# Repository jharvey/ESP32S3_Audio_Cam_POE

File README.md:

# ESP32S3_Audio_Cam_POE

This is a PCB layout for ESP32S3 with OV2640 / OV5640 camera. It was designed in KiCad 9 and converted to KiCad 10 (10.0.8); the files no longer open in KiCad 9.
The board's major features include:
* Camera.
* 2 way audio.
* Hardwired Ethernet including POE.
* Camera pan / tilt servos and lamp control.
* record to SD card.
* misc outputs to drive misc motors or similar outputs. 
* Battery powered option with Li-ion type of battery. 
* Stream video to NVR recording station. 

## Firmware
Firmware found here https://github.com/jharvey/ESP32-CAM_MJPEG2SD

Changes up to version 0.1:
* Initial layout
* Converted to KiCad 10.
* Removed the Medium and Smaller cost-reduction variants.

## Purpose

The layout design intent is to make a hardwired intercom system which includes options for camera, making a near equivalent of a doorbell camera. Hardwired means it's not susceptible to RF jamming, or similar attacks. It can be battery powered at the ethernet switch source so it can handle power outages. Lighting controls allow night time spot light, and day time spot light controls. Pan, Tilt, Rotate could potentially allow a laser pointer to distract bad players if things go bump in the night. 

## Installation
Clone with the JLCPCB library submodule, which the symbol and footprint tables point to:

```
git clone --recurse-submodules https://github.com/jharvey/ESP32S3_Audio_Cam_POE.git
```

All JLCPCB symbols, footprints and 3D models resolve from this submodule, so you do not need the JLCPCB library installed through the KiCad Plugin and Content Manager. Other 3D models use KiCad's standard `${KICAD10_3DMODEL_DIR}` library.

On Windows, if the submodule fails with "Filename too long" or "'$GIT_DIR' too big", enable long paths first (`git config --global core.longpaths true`) or clone to a shorter folder.

TBD currently has not had its first spin. TBD

## 3D case
See 3D case found here
TBD create file in OnShape and post link here. TBD

## 3D pictures from KICAD
<div align="center">

</div>

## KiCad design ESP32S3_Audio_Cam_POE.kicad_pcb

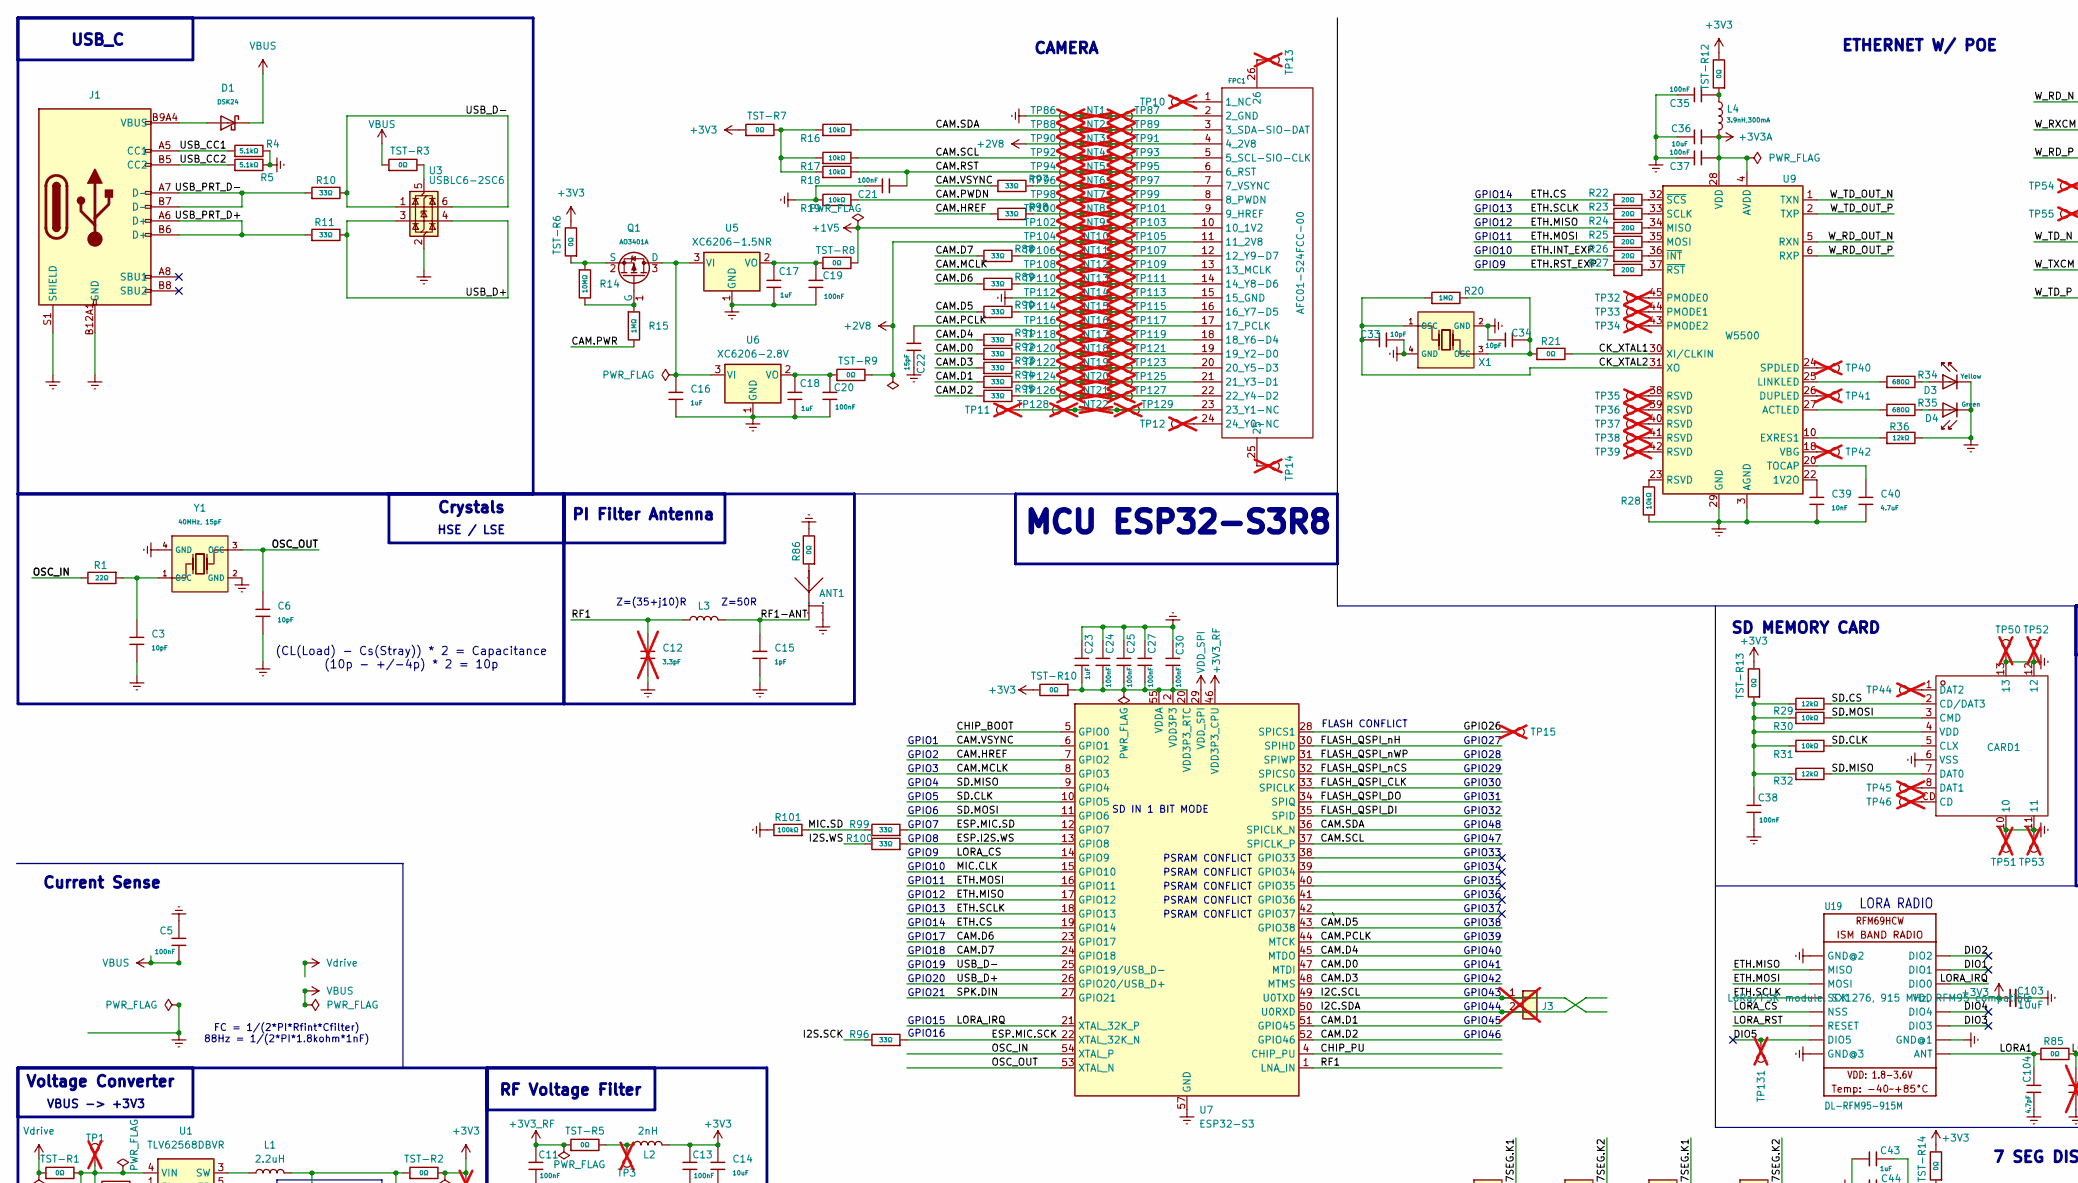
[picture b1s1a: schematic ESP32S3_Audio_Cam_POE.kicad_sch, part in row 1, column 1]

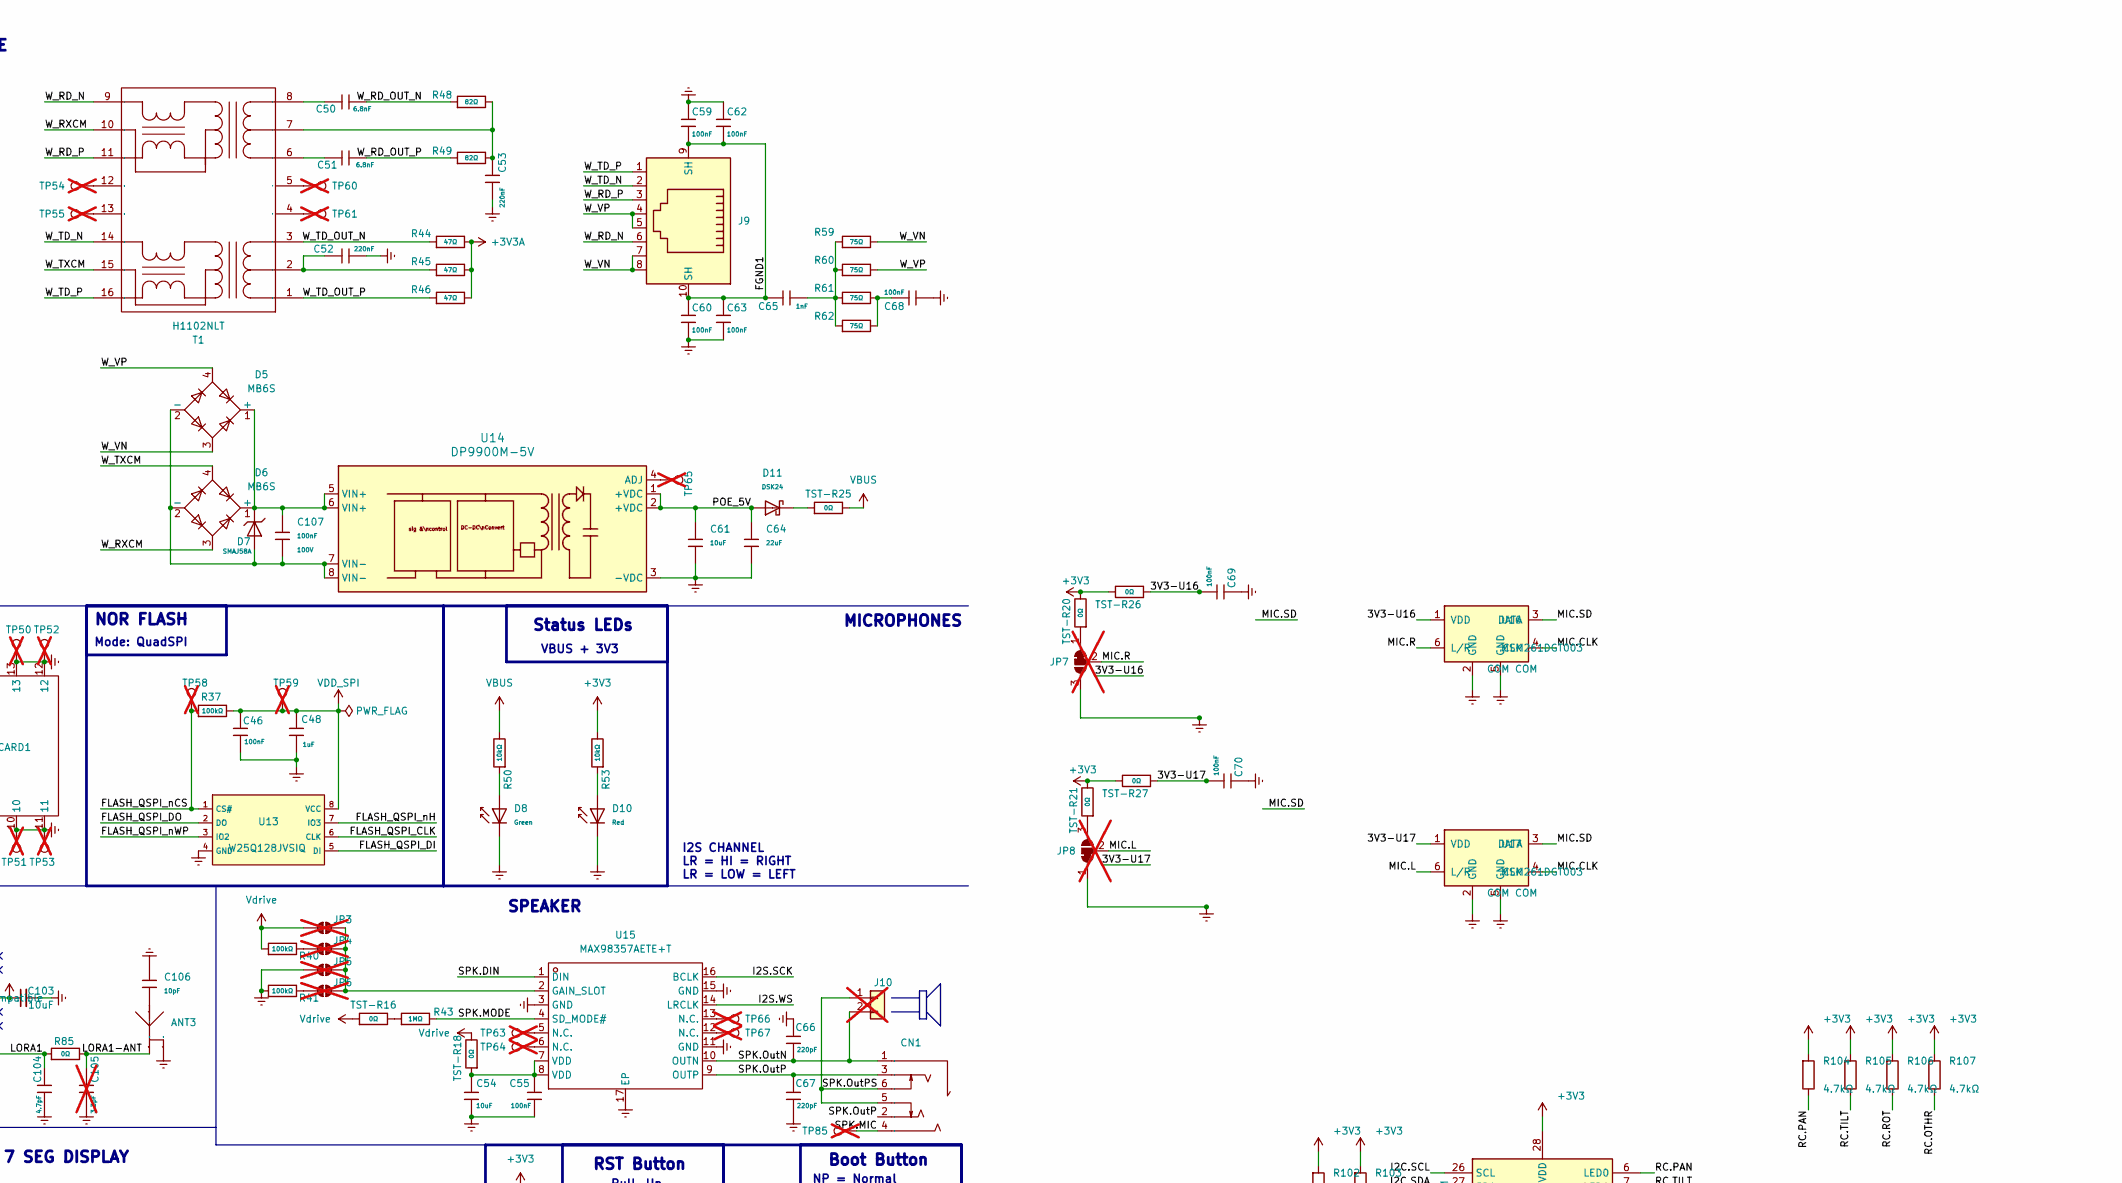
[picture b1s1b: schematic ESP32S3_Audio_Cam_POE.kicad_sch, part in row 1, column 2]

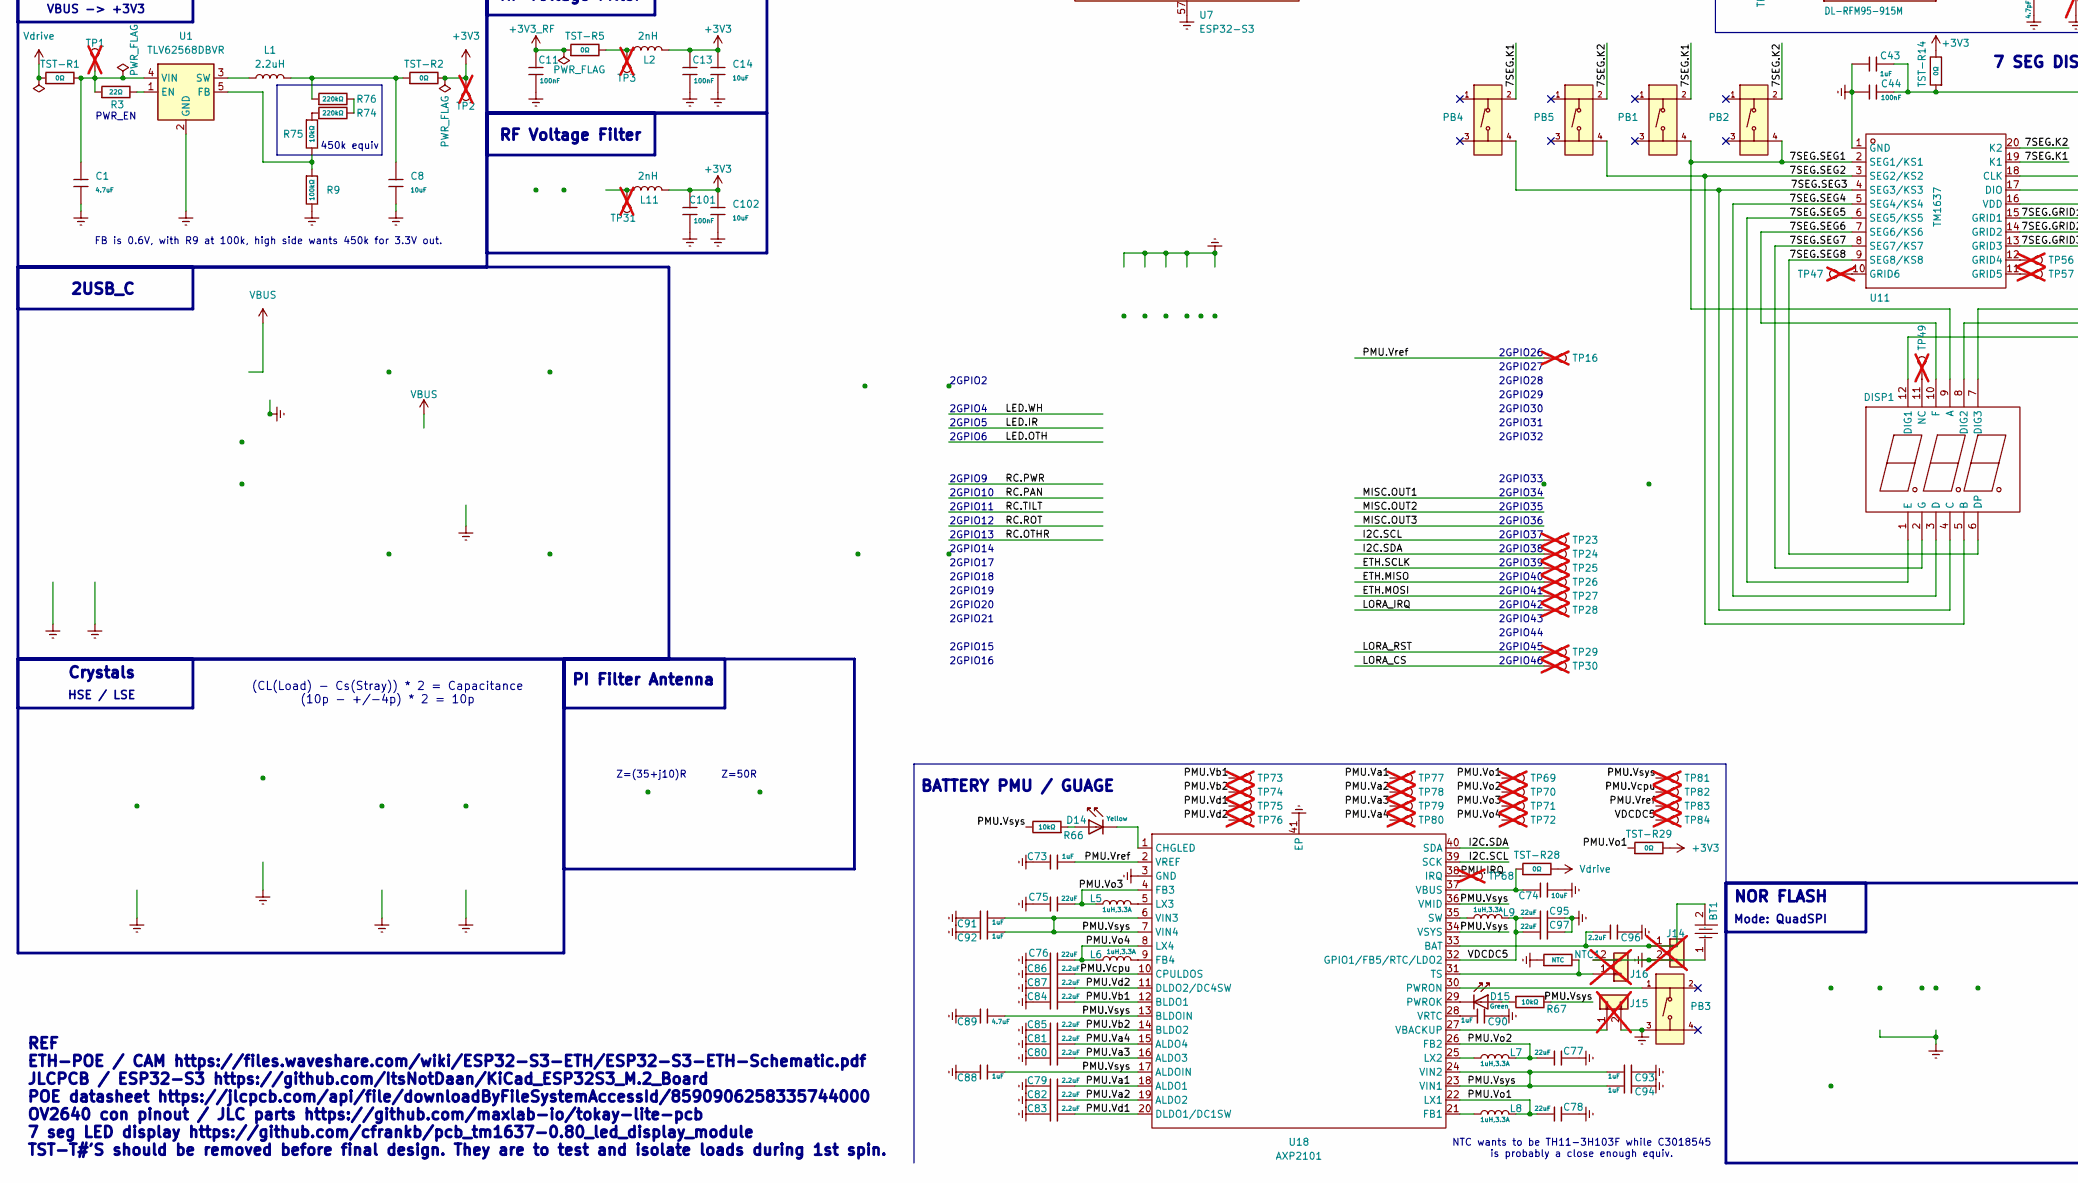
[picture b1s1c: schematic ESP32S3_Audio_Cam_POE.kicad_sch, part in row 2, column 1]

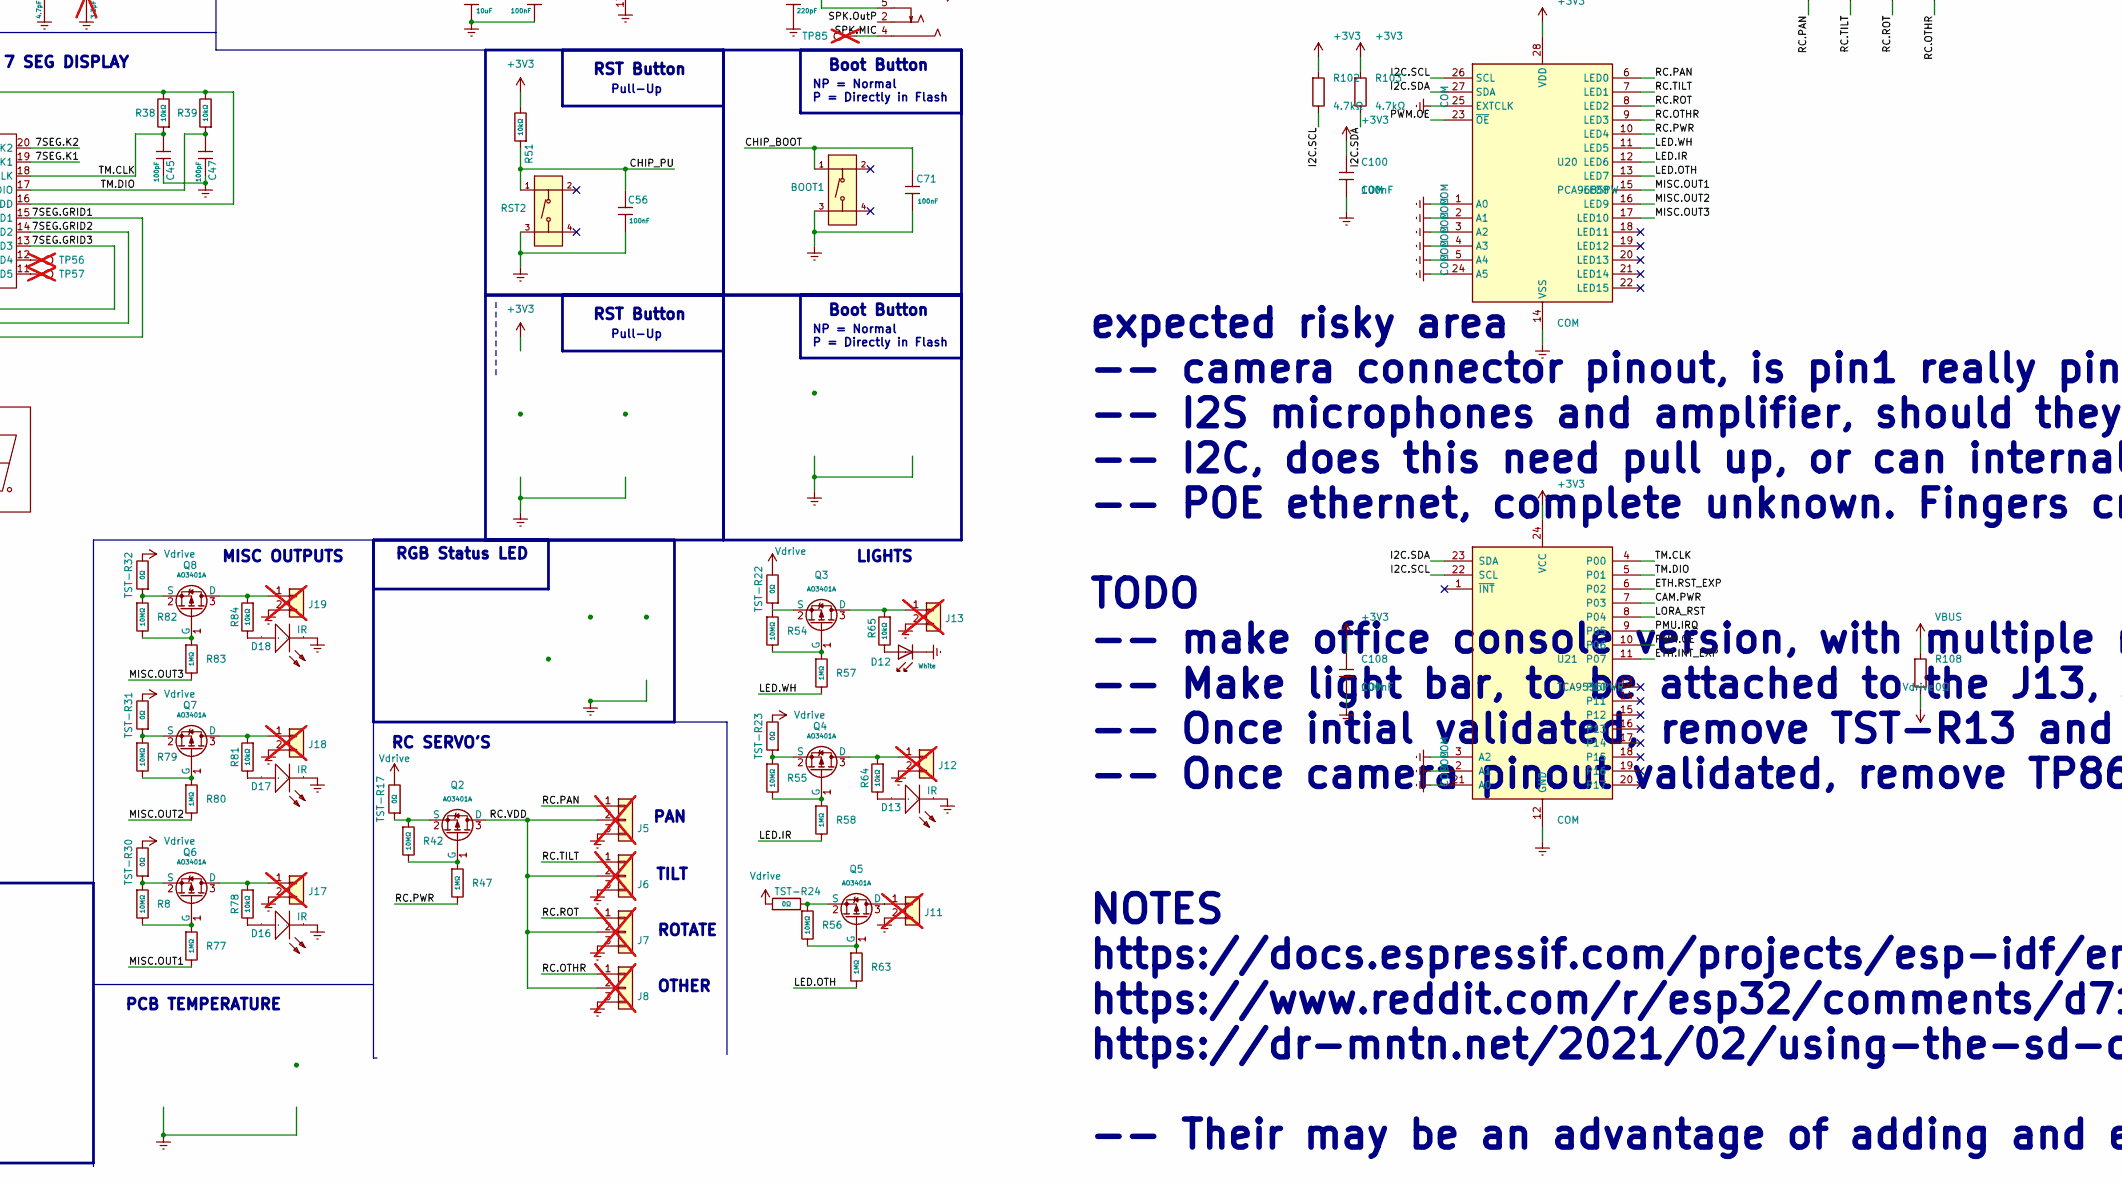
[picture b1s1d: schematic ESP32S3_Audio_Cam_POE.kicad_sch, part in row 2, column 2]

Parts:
ANT1: KH-3216-H0209; ANT-SMD_L3.2-W1.6-KH-3216F245C04; LCSC C2925417
ANT3: H2U646MHLQ0200; ANT-SMD_H2U646MHLQ0200; LCSC C5370061
BOOT1: Tactile Button, 160gf; SW-SMD_4P-L5.1-W5.1-P3.70-LS6.5-TL-2; LCSC C318884
BT1: BH-18650-B1BA002; BATTERY-SMD_18650-1S-L77.1-W20.7-1; LCSC C2988620
C1: 4.7uF; C_0805; LCSC C1779
C3, C6, C33, C34, C106: 10pF; C_0402; LCSC C32949
C5, C11, C13, C19, C20, C21, C24, C25, C27, C30, C35, C37, C38, C44, C46, C55, C56, C68, C69, C70, C71, C101: 100nF; C_0603; LCSC C14663
C8, C14, C74, C102: 10uF; C_0402; LCSC C15525
C12, C105: 3.3pF; C_0402; LCSC C1565; not fitted
C15: 1pF; C_0402; LCSC C1550
C16, C17, C18, C23, C43, C48: 1uF; C_0603; LCSC C15849
C22: 15pF; C_0402; LCSC C1548
C36, C54, C61, C103: 10uF; C_0805; LCSC C440198
C39: 10nF; C_0402; LCSC C15195
C40: 4.7uF; C_0603; LCSC C19666
C45, C47: 100pF; C_0402; LCSC C1546
C50, C51: 6.8nF; C_0603; LCSC C1631
C52, C53: 220nF; C_0603; LCSC C21120
C59, C60, C62, C63: 100nF; C_0805; LCSC C28233
C64: 22uF; C_0805; LCSC C45783
C65: 1nF; C_1206; LCSC C9196
C66, C67: 220pF; C_0402; LCSC C1530
C73, C88, C90, C91, C92, C93, C94: 1uF; C_0402; LCSC C52923
C75, C76, C77, C78, C95, C97: 22uF; C_0603; LCSC C59461
C79, C80, C81, C82, C83, C84, C85, C86, C87, C96: 2.2uF; C_0402; LCSC C12530
C89: 4.7uF; C_0402; LCSC C23733
C100, C108: 100nF; C_0603
C104: 4.7pF; C_0402; LCSC C1569
C107: 100nF; C_0805; Voltage Rated 100V; Tolerance ±10%; Part CL21B104KCFNNNE; LCSC C28233
CARD1: TF PUSH; TF-PUSH-SD-CARD_C393941; LCSC C393941
CN1: PJ-316C-6A; SMD_3.5mm_Audio_Connectors_(Headphones)_C707223; LCSC C707223
D1, D11: DSK24; D_SOD-123FL; LCSC C22466352
D3, D14: Yellow; D_0805; LCSC C2296
D4, D8, D15: Green; D_0805; LCSC C2297
D5, D6: MB6S; MB6S-C82584; LCSC C82584
D7: SMAJ58A; D_SMA; LCSC C19077554
D10: Red; D_0603; LCSC C2286
D12: White; D_0603; LCSC C2290
D13, D16, D17, D18: IR; IR-LED_C131280; LCSC C131280
DISP1: SLS0563DBA1GD; 3x7-seg_LED-RED_C2913084; LCSC C2913085
FPC1: AFC01-S24FCC-00; OV2640_connector_AFC01-S24FCC-00; LCSC C262276
J1: Connector, USB-TYPE-C-16P; TYPE-C-SMD_HX-TYPE-C-16PIN; LCSC C2927039
J3, J10, J11, J12, J13, J14, J15, J16, J17, J18, J19: Conn_01x02; PinHeader_1x02_P1.00mm_Vertical; not fitted
J5, J6, J7, J8: Conn_01x03; PinHeader_1x03_P2.54mm_Vertical; not fitted
J9: HC-RJ45-055-4_8P8C_Shielded; HC-RJ45-055-4_C3000211; LCSC C3000211
JP3, JP4, JP5, JP6: SolderJumper_2_Open; SolderJumper-2_P1.3mm_Open_TrianglePad1.0x1.5mm; not fitted
JP7, JP8: SolderJumper_3_Bridged12; SolderJumper-3_P1.3mm_Bridged12_Pad1.0x1.5mm; not fitted
L1: 2.2uH; L_Wurth_WE-LQSH-4020; LCSC C135262
L2, L11: 2nH; L_0603_1608Metric_Pad1.05x0.95mm_HandSolder; LCSC C29682
L3, L4: 3.9nH,300mA; L_0402; LCSC C14033
L5, L6, L7, L8, L9: 1uH,3.3A; L_1008_2520Metric; LCSC C435392
NT1, NT2, NT3, NT4, NT5, NT6, NT7, NT8, NT9, NT10, NT11, NT12, NT13, NT14, NT15, NT16, NT17, NT18, NT19, NT20, NT21, NT22: NetTie_2; NetTie-2_SMD_Pad0.5mm; not fitted
NTC1: NTC; R_0402; LCSC C3018545
PB1, PB2, PB3, PB4, PB5: Tactile Button, 160gf; SW-SMD_4P-L5.1-W5.1-P3.70-LS6.5-TL-2; LCSC C318884
Q1, Q2, Q3, Q4, Q5, Q6, Q7, Q8: AO3401A; Q_SOT-23; LCSC C15127
R1, R3: 22Ω; R_0402; LCSC C25092
R4, R5: 5.1kΩ; R_0402; LCSC C25905
R8, R14, R42, R54, R55, R56, R79, R82: 10MΩ; R_0402; LCSC C26082
R9, R37: 100kΩ; R_0402; LCSC C25741
R10, R11: 33Ω; R_0402; LCSC C25105
R15, R20, R43, R47, R57, R58, R63, R77, R80, R83: 1MΩ; R_0402; LCSC C26083
R16, R17, R18, R19, R28, R30, R31, R38, R39, R50, R51, R53, R64, R65, R66, R67, R75, R78, R81, R84: 10kΩ; R_0402; LCSC C25744
R21, R85, R86: 0Ω; R_0402; LCSC C17168
R22, R23, R24, R25, R26, R27: 20Ω; R_0603; LCSC C22950
R29, R32, R36: 12kΩ; R_0603; LCSC C22790
R34, R35: 680Ω; R_0402; LCSC C25130
R40, R41: 100kΩ; R_0805; LCSC C149504
R44, R45, R46: 47Ω; R_0603; LCSC C23182
R48, R49: 82Ω; R_0603; LCSC C23255
R59, R60, R61, R62: 75Ω; R_0603; LCSC C4275
R74, R76: 220kΩ; R_0402; LCSC C25767
R88, R89, R90, R91, R92, R93, R94, R95, R96, R97, R98, R99, R100: 33Ω; R_0402; Overload Voltage (Max) 50V; Tolerance ±1%; Part 0402WGF330JTCE; LCSC C25105
R101: 100kΩ; R_0402; Overload Voltage (Max) 50V; Tolerance ±1%; Part 0402WGF1003TCE; LCSC C25741
R102, R103, R104, R105, R106, R107: 4.7kΩ; R_0402; LCSC C25900
R108: 0Ω; R_1206; LCSC C17888
RST2: Tactile Button, 160gf; SW-SMD_4P-L5.1-W5.1-P3.70-LS6.5-TL-2; LCSC C318884
T1: H1102NLT; H1102NLT_C18584; LCSC C18584
TP1, TP2, TP3, TP10, TP11, TP12, TP15, TP16, TP23, TP24, TP25, TP26, TP27, TP28, TP29, TP30, TP31, TP32, TP33, TP34, TP35, TP36, TP37, TP38, TP39, TP40, TP41, TP42, TP44, TP45, TP46, TP47, TP49, TP54, TP55, TP56, TP57, TP58, TP59, TP60, TP61, TP63, TP64, TP65, TP66, TP67, TP68, TP85, TP131: TestPoint; TestPoint_Pad_D1.0mm; not fitted
TP13, TP14, TP50, TP51, TP52, TP53: TestPoint; TestPoint_Plated_Hole_D2.0mm; not fitted
TP69, TP70, TP71, TP72, TP73, TP74, TP75, TP76, TP77, TP78, TP79, TP80, TP81, TP82, TP83, TP84, TP86, TP87, TP88, TP89, TP90, TP91, TP92, TP93, TP94, TP95, TP96, TP97, TP98, TP99, TP100, TP101, TP102, TP103, TP104, TP105, TP106, TP107, TP108, TP109, TP110, TP111, TP112, TP113, TP114, TP115, TP116, TP117, TP118, TP119, TP120, TP121, TP122, TP123, TP124, TP125, TP126, TP127, TP128, TP129: TestPoint; PinHeader_1x01_P1.00mm_Vertical; not fitted
TST-R1, TST-R2, TST-R3, TST-R5, TST-R6, TST-R7, TST-R8, TST-R9, TST-R10, TST-R12, TST-R13, TST-R14, TST-R16, TST-R17, TST-R18, TST-R20, TST-R21, TST-R22, TST-R23, TST-R24, TST-R25, TST-R26, TST-R27, TST-R28, TST-R29, TST-R30, TST-R31, TST-R32: 0Ω; R_0603; LCSC C21189
U1: TLV62568DBVR; SOT-23-5; LCSC C163219
U3: USBLC6-2SC6; SOT-23-6; LCSC C2827654
U5: XC6206-1.5NR; SOT-23-3; LCSC C2984869
U6: XC6206-2.8V; SOT-23-3; LCSC C41424780
U7: ESP32-S3; QFN-56-1EP_7x7mm_P0.4mm_EP4x4mm_ThermalVias; LCSC C2913194
U9: W5500; LQFP-48_7x7mm_P0.5mm; LCSC C32843
U11: TM1637; digital tube drivers_c2962580; LCSC C5337160
U13: W25Q128JVSIQ; SOIC-8_L5.3-W5.3-P1.27-LS8.0-BL; LCSC C97521
U14: DP9900M-5V; DP9900M_C5380106; LCSC C5380106
U15: MAX98357AETE+T; MAX98357AETE+T_C910544; LCSC C910544
U16, U17: MSM261DGT003; LGA-6_2.0x4.0mm_MSM261DGT003; LCSC C48227730
U18: AXP2101; QFN-40-1EP_5x5mm_P0.4mm_EP3.6x3.6mm_ThermalVias; LCSC C3036461
U19: DL-RFM95-915M; RFM69HCW; LCSC C2844473
U20: PCA9685PW; TSSOP-28_4.4x9.7mm_P0.65mm; LCSC C2678753
U21: TCA9555PWR; TSSOP-24_4.4x7.8mm_P0.65mm; LCSC C465732
X1: X322525MOB4SI; OSC-SMD_4P-L3.2-W2.5-BL; LCSC C9006
Y1: 40MHz, 15pF; OSC-SMD_4P-L3.2-W2.5-BL_SIT8008BI; LCSC C9010

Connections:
+1V5: NT9.1, TP102.1, TST-R8.2
+2V8: NT3.1, NT10.1, TP90.1, TP104.1, TST-R9.2
+3V3: C13.2, C14.1, C100.1, C101.2, C102.1, C103.1, C108.1, L2.2, L11.2, R51.2, R53.2, R102.1, R103.1, R104.1, R105.1, R106.1, R107.1, TP2.1, TST-R2.2, TST-R6.2, TST-R7.1, TST-R10.2, TST-R12.2, TST-R13.2, TST-R14.2, TST-R20.2, TST-R21.2, TST-R26.2, TST-R27.2, TST-R29.2, U19.5 (VDD), U20.28 (VDD), U21.24 (VCC)
+3V3A: C36.2, C37.2, L4.1, R44.2, R45.2, R46.2, U9.4 (AVDD), U9.8 (AVDD), U9.11 (AVDD), U9.15 (AVDD), U9.17 (AVDD), U9.21 (AVDD), U9.28 (VDD)
+3V3_RF: C11.2, TST-R5.1, U7.46 (VDD3P3_CPU)
/3V3-U16: C69.1, TST-R26.1, U16.1 (VDD)
/3V3-U17: C70.1, TST-R27.1, U17.1 (VDD)
/7SEG.GRID1: DISP1.12 (DIG1), U11.15 (GRID1)
/7SEG.GRID2: DISP1.8 (DIG2), U11.14 (GRID2)
/7SEG.GRID3: DISP1.7 (DIG3), U11.13 (GRID3)
/7SEG.K1: PB1.2 (B), PB4.2 (B), U11.19 (K1)
/7SEG.K2: PB2.2 (B), PB5.2 (B), U11.20 (K2)
/7SEG.SEG1: DISP1.9 (A), PB1.4 (D), PB2.4 (D), U11.2 (SEG1/KS1)
/7SEG.SEG2: DISP1.5 (B), PB5.4 (D), U11.3 (SEG2/KS2)
/7SEG.SEG3: DISP1.4 (C), PB4.4 (D), U11.4 (SEG3/KS3)
/7SEG.SEG4: DISP1.3 (D), U11.5 (SEG4/KS4)
/7SEG.SEG5: DISP1.1 (E), U11.6 (SEG5/KS5)
/7SEG.SEG6: DISP1.10 (F), U11.7 (SEG6/KS6)
/7SEG.SEG7: DISP1.2 (G), U11.8 (SEG7/KS7)
/7SEG.SEG8: DISP1.6 (DP), U11.9 (SEG8/KS8)
/CAM.D0: R92.1, U7.47 (MTDI)
/CAM.D1: R94.1, U7.51 (GPIO45)
/CAM.D2: R95.1, U7.52 (GPIO46)
/CAM.D3: R93.1, U7.48 (MTMS)
/CAM.D4: R91.1, U7.45 (MTDO)
/CAM.D5: R90.1, U7.43 (GPIO38)
/CAM.D6: R89.1, U7.23 (GPIO17)
/CAM.D7: R88.1, U7.24 (GPIO18)
/CAM.HREF: R98.1, U7.7 (GPIO2)
/CAM.MCLK: NT12.1, TP108.1, U7.8 (GPIO3)
/CAM.PCLK: C22.2, NT16.1, TP116.1, U7.44 (MTCK)
/CAM.PWDN: NT7.1, R19.2, TP98.1
/CAM.PWR: R15.2, U21.7 (P03)
/CAM.RST: C21.2, NT5.1, R18.2, TP94.1
/CAM.SCL: NT4.1, R17.2, TP92.1, U7.37 (SPICLK_P)
/CAM.SDA: NT2.1, R16.2, TP88.1, U7.36 (SPICLK_N)
/CAM.VSYNC: R97.1, U7.6 (GPIO1)
/CHIP_BOOT: BOOT1.1 (A), C71.2, U7.5 (GPIO0)
/CHIP_PU: C56.2, R51.1, RST2.1 (A), U7.4 (CHIP_PU)
/CK_XTAL1: R21.2, U9.30 (XI/CLKIN)
/CK_XTAL2: C33.1, R20.1, U9.31 (XO), X1.1 (OSC)
/DIO1: U19.7 (DIO1)
/DIO2: U19.8 (DIO2)
/DIO3: U19.3 (DIO3)
/DIO4: U19.4 (DIO4)
/DIO5: TP131.1, U19.15 (DIO5)
/ESP.I2S.WS: R100.1, U7.13 (GPIO8)
/ESP.MIC.SCK: R96.1, U7.22 (XTAL_32K_N)
/ESP.MIC.SD: R99.1, U7.12 (GPIO7)
/ETH.CS: R22.1, U7.19 (GPIO14)
/ETH.INT_EXP: R26.1, U21.11 (P07)
/ETH.MISO: R24.1, TP26.1, U7.17 (GPIO12), U19.10 (MISO)
/ETH.MOSI: R25.1, TP27.1, U7.16 (GPIO11), U19.11 (MOSI)
/ETH.RST_EXP: R27.1, U21.6 (P02)
/ETH.SCLK: R23.1, TP25.1, U7.18 (GPIO13), U19.12 (SCK)
/FGND1: C59.2, C60.1, C62.2, C63.1, C65.1, J9.9 (SH), J9.10 (SH)
/FLASH_QSPI_CLK: U7.33 (SPICLK), U13.6 (CLK)
/FLASH_QSPI_DI: U7.35 (SPID), U13.5 (DI)
/FLASH_QSPI_DO: U7.34 (SPIQ), U13.2 (DO)
/FLASH_QSPI_nCS: R37.1, TP58.1, U7.32 (SPICS0), U13.1 (CS#)
/FLASH_QSPI_nH: U7.30 (SPIHD), U13.7 (IO3)
/FLASH_QSPI_nWP: U7.31 (SPIWP), U13.3 (IO2)
/GPIO26: TP15.1, U7.28 (SPICS1)
/I2C.SCL: J3.1, R102.2, TP23.1, U7.49 (U0TXD), U18.39 (SCK), U20.26 (SCL), U21.22 (SCL)
/I2C.SDA: J3.2, R103.2, TP24.1, U7.50 (U0RXD), U18.40 (SDA), U20.27 (SDA), U21.23 (SDA)
/I2S.SCK: R96.2, U15.16 (BCLK)
/I2S.WS: R100.2, U15.14 (LRCLK)
/LED.IR: R58.2, U20.12 (LED6)
/LED.OTH: R63.2, U20.13 (LED7)
/LED.WH: R57.2, U20.11 (LED5)
/LORA1: C104.1, R85.1, U19.1 (ANT)
/LORA1-ANT: ANT3.1 (ANT), C105.1, R85.2
/LORA_CS: TP30.1, U7.14 (GPIO9), U19.13 (NSS)
/LORA_IRQ: TP28.1, U7.21 (XTAL_32K_P), U19.6 (DIO0)
/LORA_RST: TP29.1, U19.14 (RESET), U21.8 (P04)
/MIC.CLK: U7.15 (GPIO10), U16.4 (CLK), U17.4 (CLK)
/MIC.L: JP8.2 (C), U17.6 (L/R)
/MIC.R: JP7.2 (C), U16.6 (L/R)
/MIC.SD: R99.2, R101.1, U16.3 (DATA), U17.3 (DATA)
/MISC.OUT1: R77.2, U20.15 (LED8)
/MISC.OUT2: R80.2, U20.16 (LED9)
/MISC.OUT3: R83.2, U20.17 (LED10)
/OSC_IN: R1.2, U7.54 (XTAL_P)
/OSC_OUT: C6.1, U7.53 (XTAL_N), Y1.3 (OSC)
/PMU.IRQ: TP68.1, U18.38 (IRQ), U21.9 (P05)
/PMU.Va1: C79.2, TP77.1, U18.18 (ALDO1)
/PMU.Va2: C82.2, TP78.1, U18.19 (ALDO2)
/PMU.Va3: C80.2, TP79.1, U18.16 (ALDO3)
/PMU.Va4: C81.2, TP80.1, U18.15 (ALDO4)
/PMU.Vb1: C84.2, TP73.1, U18.12 (BLDO1)
/PMU.Vb2: C85.2, TP74.1, U18.14 (BLDO2)
/PMU.Vcpu: C86.2, TP82.1, U18.10 (CPULDOS)
/PMU.Vd1: C83.2, TP75.1, U18.20 (DLDO1/DC1SW)
/PMU.Vd2: C87.2, TP76.1, U18.11 (DLDO2/DC4SW)
/PMU.Vo1: C78.2, L8.1, TP69.1, TST-R29.1, U18.22 (LX1)
/PMU.Vo2: C77.2, L7.1, TP70.1, U18.26 (FB2)
/PMU.Vo3: C75.2, L5.1, TP71.1, U18.4 (FB3)
/PMU.Vo4: C76.2, L6.1, TP72.1, U18.8 (LX4)
/PMU.Vref: C73.2, TP16.1, TP83.1, U18.2 (VREF)
/PMU.Vsys: C88.2, C89.2, C91.2, C92.2, C93.2, C94.2, R66.2, R67.2, TP81.1, U18.6 (VIN3), U18.7 (VIN4), U18.13 (BLDOIN), U18.17 (ALDOIN), U18.23 (VIN1), U18.24 (VIN2), U18.34 (VSYS), U18.36 (VMID)
/POE_5V: C61.1, C64.1, D11.2, U14.1 (+VDC), U14.2 (+VDC)
/PWM.OE: U20.23 (~OE), U21.10 (P06)
/RC.OTHR: J8.1, R107.2, U20.9 (LED3)
/RC.PAN: J5.1, R104.2, U20.6 (LED0)
/RC.PWR: R47.2, U20.10 (LED4)
/RC.ROT: J7.1, R106.2, U20.8 (LED2)
/RC.TILT: J6.1, R105.2, U20.7 (LED1)
/RC.VDD: J5.2, J6.2, J7.2, J8.2, Q2.3 (D)
/RF1: C12.1, L3.1, U7.1 (LNA_IN)
/RF1-ANT: ANT1.1 (ANT), C15.1, L3.2
/SD.CLK: CARD1.5 (CLX), R31.2, U7.10 (GPIO5)
/SD.CS: CARD1.2 (CD/DAT3), R29.2
/SD.MISO: CARD1.7 (DAT0), R32.2, U7.9 (GPIO4)
/SD.MOSI: CARD1.3 (CMD), R30.2, U7.11 (GPIO6)
/SPK.DIN: U7.27 (GPIO21), U15.1 (DIN)
/SPK.MIC: CN1.4, TP85.1
/SPK.MODE: R43.2, U15.4 (SD_MODE#)
/SPK.OutN: C66.2, CN1.1, J10.2, U15.10 (OUTN)
/SPK.OutP: C67.1, CN1.2, CN1.3, U15.9 (OUTP)
/SPK.OutPS: CN1.5, CN1.6, J10.1
/TM.CLK: C45.2, R38.1, U11.18 (CLK), U21.4 (P00)
/TM.DIO: C47.2, R39.1, U11.17 (DIO), U21.5 (P01)
/USB_CC1: J1.A5 (CC1), R4.1
/USB_CC2: J1.B5 (CC2), R5.1
/USB_D+: R11.2, U3.3 (I/O2), U3.4 (I/O2), U7.26 (GPIO20/USB_D+)
/USB_D-: R10.2, U3.1 (I/O1), U3.6 (I/O1), U7.25 (GPIO19/USB_D-)
/USB_PRT_D+: J1.A6 (D+), J1.B6 (D+), R11.1
/USB_PRT_D-: J1.A7 (D-), J1.B7 (D-), R10.1
/VDCDC5: C95.2, C97.2, L9.1, TP84.1, U18.32 (GPIO1/FB5/RTC/LDO2)
/W_RD_N: J9.6, T1.9
/W_RD_OUT_N: C50.2, R48.1, U9.5 (RXN)
/W_RD_OUT_P: C51.2, R49.1, U9.6 (RXP)
/W_RD_P: J9.3, T1.11
/W_RXCM: D6.3, T1.10
/W_TD_N: J9.2, T1.14
/W_TD_OUT_N: R44.1, T1.3, U9.1 (TXN)
/W_TD_OUT_P: R46.1, T1.1, U9.2 (TXP)
/W_TD_P: J9.1, T1.16
/W_TXCM: D6.4, T1.15
/W_VN: D5.3, J9.7, J9.8, R59.2
/W_VP: D5.4, J9.4, J9.5, R60.2
COM: ANT1.3 (ANT), ANT3.3 (ANT), BOOT1.3 (C), BT1.1, C1.2, C3.2, C5.2, C6.2, C8.2, C11.1, C12.2, C13.1, C14.2, C15.2, C16.2, C17.2, C18.2, C19.1, C20.1, C21.1, C22.1, C23.1, C24.2, C25.2, C27.2, C30.2, C33.2, C34.1, C35.1, C36.1, C37.1, C38.1, C39.2, C40.2, C43.1, C44.2, C45.1, C46.1, C47.1, C48.2, C52.2, C53.2, C54.2, C55.2, C56.1, C59.1, C60.2, C61.2, C62.1, C63.2, C64.2, C66.1, C67.2, C68.2, C69.2, C70.2, C71.1, C73.1, C74.2, C75.1, C76.1, C77.1, C78.1, C79.1, C80.1, C81.1, C82.1, C83.1, C84.1, C85.1, C86.1, C87.1, C88.1, C89.1, C90.1, C91.1, C92.1, C93.1, C94.1, C95.1, C96.1, C97.1, C100.2, C101.1, C102.2, C103.2, C104.2, C105.2, C106.1, C108.2, CARD1.6 (VSS), CARD1.10, CARD1.11, CARD1.12, CARD1.13, D3.1, D4.1, D8.1, D10.1, D12.1, D13.1 (C), D16.1 (C), D17.1 (C), D18.1 (C), J1.A12B1 (GND), J1.B12A1 (GND), J1.S1 (SHIELD), J5.3, J6.3, J7.3, J8.3, J11.2, J12.2, J13.2, J14.2, J15.2, J16.2, J17.2, J18.2, J19.2, JP5.1 (A), JP7.3 (B), JP8.1 (A), NT1.1, NT14.1, NTC1.1, PB3.3 (C), R4.2, R5.2, R9.2, R19.1, R28.2, R36.2, R41.1, R86.2, R101.2, RST2.3 (C), TP50.1, TP51.1, TP52.1, TP53.1, TP86.1, TP112.1, U1.2 (GND), U3.2 (GND), U5.1 (GND), U6.1 (GND), U7.57 (GND), U9.3 (AGND), U9.9 (AGND), U9.14 (AGND), U9.16 (AGND), U9.19 (AGND), U9.29 (GND), U9.48 (AGND), U11.1 (GND), U13.4 (GND), U14.3 (-VDC), U15.3 (GND), U15.11 (GND), U15.15 (GND), U15.17 (EP), U16.2 (GND), U16.5 (GND), U17.2 (GND), U17.5 (GND), U18.3 (GND), U18.41 (EP), U19.2 (GND@1), U19.9 (GND@2), U19.16 (GND@3), U20.1 (A0), U20.2 (A1), U20.3 (A2), U20.4 (A3), U20.5 (A4), U20.14 (VSS), U20.24 (A5), U20.25 (EXTCLK), U21.2 (A1), U21.3 (A2), U21.12 (GND), U21.21 (A0), X1.2 (GND), X1.4 (GND), Y1.2 (GND), Y1.4 (GND)
unnamed: ANT1.2, R86.1
unnamed: ANT3.2, C106.2
unnamed: C3.1, R1.1, Y1.1 (OSC)
unnamed: C8.1, L1.2, R76.1, TST-R2.1
unnamed: C34.2, R20.2, R21.1, X1.3 (OSC)
unnamed: C35.2, L4.2, TST-R12.1
unnamed: C50.1, T1.8
unnamed: C51.1, T1.6
unnamed: C52.1, R45.1, T1.2
unnamed: C53.1, R48.2, R49.2, T1.7
unnamed: C54.1, C55.1, TST-R18.1, U15.7 (VDD), U15.8 (VDD)
unnamed: C65.2, R59.1, R60.1, R61.1, R62.1
unnamed: C68.1, R61.2, R62.2
unnamed: CARD1.8 (DAT1), TP45.1
unnamed: CARD1.1 (DAT2), TP44.1
unnamed: CARD1.CD, TP46.1
unnamed: C38.2, CARD1.4 (VDD), R29.1, R30.1, R31.1, R32.1, TST-R13.1
unnamed: D1.2, J1.A9B4 (VBUS), J1.B9A4 (VBUS)
unnamed: D3.2, R34.2
unnamed: D4.2, R35.2
unnamed: C107.1, D5.1 (+), D6.1 (+), D7.1, U14.5 (VIN+), U14.6 (VIN+)
unnamed: C107.2, D5.2 (-), D6.2 (-), D7.2, U14.7 (VIN-), U14.8 (VIN-)
unnamed: D8.2, R50.1
unnamed: D10.2, R53.1
unnamed: D11.1, TST-R25.1
unnamed: D12.2, R65.2
unnamed: D13.2 (A), R64.2
unnamed: D14.2, R66.1
unnamed: D15.2, R67.1
unnamed: D16.2 (A), R78.2
unnamed: D17.2 (A), R81.2
unnamed: D18.2 (A), R84.2
unnamed: DISP1.11 (NC), TP49.1
unnamed: FPC1.1 (1_NC), TP10.1
unnamed: FPC1.2 (2_GND), NT1.2, TP87.1
unnamed: FPC1.3 (3_SDA-SIO-DAT), NT2.2, TP89.1
unnamed: FPC1.4 (4_2V8), NT3.2, TP91.1
unnamed: FPC1.5 (5_SCL-SIO-CLK), NT4.2, TP93.1
unnamed: FPC1.6 (6_RST), NT5.2, TP95.1
unnamed: FPC1.7 (7_VSYNC), NT6.2, TP97.1
unnamed: FPC1.8 (8_PWDN), NT7.2, TP99.1
unnamed: FPC1.9 (9_HREF), NT8.2, TP101.1
unnamed: FPC1.10 (10_1V2), NT9.2, TP103.1
unnamed: FPC1.11 (11_2V8), NT10.2, TP105.1
unnamed: FPC1.12 (12_Y9-D7), NT11.2, TP107.1
unnamed: FPC1.13 (13_MCLK), NT12.2, TP109.1
unnamed: FPC1.14 (14_Y8-D6), NT13.2, TP111.1
unnamed: FPC1.15 (15_GND), NT14.2, TP113.1
unnamed: FPC1.16 (16_Y7-D5), NT15.2, TP115.1
unnamed: FPC1.17 (17_PCLK), NT16.2, TP117.1
unnamed: FPC1.18 (18_Y6-D4), NT17.2, TP119.1
unnamed: FPC1.19 (19_Y2-D0), NT18.2, TP121.1
unnamed: FPC1.20 (20_Y5-D3), NT19.2, TP123.1
unnamed: FPC1.21 (21_Y3-D1), NT20.2, TP125.1
unnamed: FPC1.22 (22_Y4-D2), NT21.2, TP127.1
unnamed: FPC1.23 (23_Y1-NC), NT22.2, TP129.1
unnamed: FPC1.24 (24_Y0-NC), TP12.1
unnamed: FPC1.25, TP14.1
unnamed: FPC1.26, TP13.1
unnamed: J11.1, Q5.3 (D)
unnamed: J12.1, Q4.3 (D), R64.1
unnamed: J13.1, Q3.3 (D), R65.1
unnamed: BT1.2, C96.2, J14.1, U18.33 (BAT)
unnamed: J15.1, U18.27 (VBACKUP)
unnamed: J16.1, NTC1.2, U18.31 (TS)
unnamed: J17.1, Q6.3 (D), R78.1
unnamed: J18.1, Q7.3 (D), R81.1
unnamed: J19.1, Q8.3 (D), R84.1
unnamed: JP3.2 (B), JP4.2 (B), JP5.2 (B), JP6.2 (B), U15.2 (GAIN_SLOT)
unnamed: JP4.1 (A), R40.2
unnamed: JP6.1 (A), R41.2
unnamed: JP7.1 (A), TST-R20.1
unnamed: JP8.3 (B), TST-R21.1
unnamed: L2.1, TP3.1, TST-R5.2
unnamed: L11.1, TP31.1
unnamed: NT6.1, R97.2, TP96.1
unnamed: NT8.1, R98.2, TP100.1
unnamed: NT11.1, R88.2, TP106.1
unnamed: NT13.1, R89.2, TP110.1
unnamed: NT15.1, R90.2, TP114.1
unnamed: NT17.1, R91.2, TP118.1
unnamed: NT18.1, R92.2, TP120.1
unnamed: NT19.1, R93.2, TP122.1
unnamed: NT20.1, R94.2, TP124.1
unnamed: NT21.1, R95.2, TP126.1
unnamed: NT22.1, TP11.1, TP128.1
unnamed: PB3.1 (A), U18.30 (PWRON)
unnamed: C16.1, Q1.3 (D), U5.3 (VI), U6.3 (VI)
unnamed: Q1.1 (G), R14.2, R15.1
unnamed: Q1.2 (S), R14.1, TST-R6.1
unnamed: Q2.1 (G), R42.2, R47.1
unnamed: Q2.2 (S), R42.1, TST-R17.1
unnamed: Q3.1 (G), R54.2, R57.1
unnamed: Q3.2 (S), R54.1, TST-R22.1
unnamed: Q4.1 (G), R55.2, R58.1
unnamed: Q4.2 (S), R55.1, TST-R23.1
unnamed: Q5.1 (G), R56.2, R63.1
unnamed: Q5.2 (S), R56.1, TST-R24.2
unnamed: Q6.1 (G), R8.2, R77.1
unnamed: Q6.2 (S), R8.1, TST-R30.1
unnamed: Q7.1 (G), R79.2, R80.1
unnamed: Q7.2 (S), R79.1, TST-R31.1
unnamed: Q8.1 (G), R82.2, R83.1
unnamed: Q8.2 (S), R82.1, TST-R32.1
unnamed: R16.1, R17.1, R18.1, TST-R7.2
unnamed: R28.1, U9.23 (RSVD)
unnamed: R43.1, TST-R16.2
unnamed: R74.1, R75.1
unnamed: R74.2, R76.2
unnamed: T1.4, TP61.1
unnamed: T1.5, TP60.1
unnamed: T1.12, TP54.1
unnamed: T1.13, TP55.1
unnamed: TP35.1, U9.38 (RSVD)
unnamed: TP36.1, U9.39 (RSVD)
unnamed: TP37.1, U9.40 (RSVD)
unnamed: TP38.1, U9.41 (RSVD)
unnamed: TP39.1, U9.42 (RSVD)
unnamed: TP63.1, U15.5 (N.C.)
unnamed: TP64.1, U15.6 (N.C.)
unnamed: TP66.1, U15.13 (N.C.)
unnamed: TP67.1, U15.12 (N.C.)
unnamed: R3.2, U1.1 (EN)
unnamed: R9.1, R75.2, U1.5 (FB)
unnamed: L1.1, U1.3 (SW)
unnamed: C1.1, R3.1, TP1.1, TST-R1.2, U1.4 (VIN)
unnamed: TST-R3.2, U3.5 (VBUS)
unnamed: C17.1, C19.2, TST-R8.1, U5.2 (VO)
unnamed: C18.1, C20.2, TST-R9.1, U6.2 (VO)
unnamed: C23.2, C24.1, C25.1, C27.1, C30.1, TST-R10.1, U7.2 (VDD3P3), U7.3 (VDD3P3), U7.20 (VDD3P3_RTC), U7.55 (VDDA), U7.56 (VDDA)
unnamed: C39.1, U9.22 (1V2O)
unnamed: R35.1, U9.27 (ACTLED)
unnamed: TP41.1, U9.26 (DUPLED)
unnamed: R36.1, U9.10 (EXRES1)
unnamed: R34.1, U9.25 (LINKLED)
unnamed: R24.2, U9.34 (MISO)
unnamed: R25.2, U9.35 (MOSI)
unnamed: TP32.1, U9.45 (PMODE0)
unnamed: TP33.1, U9.44 (PMODE1)
unnamed: TP34.1, U9.43 (PMODE2)
unnamed: R23.2, U9.33 (SCLK)
unnamed: TP40.1, U9.24 (SPDLED)
unnamed: C40.1, U9.20 (TOCAP)
unnamed: TP42.1, U9.18 (VBG)
unnamed: R26.2, U9.36 (~INT)
unnamed: R27.2, U9.37 (~RST)
unnamed: R22.2, U9.32 (~SCS)
unnamed: TP56.1, U11.12 (GRID4)
unnamed: TP57.1, U11.11 (GRID5)
unnamed: TP47.1, U11.10 (GRID6)
unnamed: C43.2, C44.1, R38.2, R39.2, TST-R14.1, U11.16 (VDD)
unnamed: TP65.1, U14.4 (ADJ)
unnamed: D14.1, U18.1 (CHGLED)
unnamed: L8.2, U18.21 (FB1)
unnamed: L6.2, U18.9 (FB4)
unnamed: L7.2, U18.25 (LX2)
unnamed: L5.2, U18.5 (LX3)
unnamed: D15.1, U18.29 (PWROK)
unnamed: L9.2, U18.35 (SW)
unnamed: C74.1, TST-R28.1, U18.37 (VBUS)
unnamed: C90.2, U18.28 (VRTC)
VBUS: C5.1, D1.1, R50.2, R108.1, TST-R3.1, TST-R25.2
VDD_SPI: C46.2, C48.1, R37.2, TP59.1, U7.29 (VDD_SPI), U13.8 (VCC)
Vdrive: JP3.1 (A), R40.1, R108.2, TST-R1.1, TST-R16.1, TST-R17.2, TST-R18.2, TST-R22.2, TST-R23.2, TST-R24.1, TST-R28.2, TST-R30.2, TST-R31.2, TST-R32.2

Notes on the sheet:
MISC OUTPUTS
Z=(35+j10)R
BATTERY PMU / GUAGE
GPIO15
2GPIO10
RGB Status LED
GPIO10
2GPIO21
GPIO28
RST Button
expected risky area -- camera connector pinout, is pin1 really pin 1 not 24? -- I2S microphones and amplifier, should they be the same lines like code suggests -- I2C, does this need pull up, or can internal pullup suffice? -- POE ethernet, complete unknown. Fingers crossed. TODO -- make office con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
GPIO31
2GPIO13
FB is 0.6V, with R9 at 100k, high side wants 450k for 3.3V out.
GPIO4
OTHER
VBUS + 3V3
GPIO21
GPIO12
NOR FLASH
2GPIO39
(CL(Load) - Cs(Stray)) * 2 = Capacitance (10p - +/-4p) * 2 = 10p
MICROPHONES
GPIO46
2GPIO2
GPIO6
TILT
2GPIO18
2GPIO31
GPIO13
GPIO14
Boot Button
2GPIO20
2GPIO36
Current Sense
Crystals
GPIO36
NP = Normal P = Directly in Flash
HSE / LSE
GPIO30
